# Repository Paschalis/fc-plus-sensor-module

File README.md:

# FC Plus Sensor Module

**FC Plus** is a modular add-on board designed for UAV flight controllers, providing advanced telemetry, GPS, object avoidance (ToF, Sonar, IR), and LED indicators for status feedback. This repository contains the necessary documentation, hardware setup guides, sensor integration instructions, and communication protocols (LoRa/WiFi) to enhance UAV autonomy and safety.

# Board Designs Overview

This repository contains a collection of **FC Plus Sensor Modules Boards** categorized by their transmission modes. More details about the transmission modes can be found in the [Transmission Modes Classification](SensorFCPlus/README.md).

> **Note:** The PCB colors are used to visually distinguish the boards. The **Antenna Diversity** boards feature **yellow** PCBs, while the **True Diversity** boards are **blue**. The **Gemini Mode** boards are marked with **red** PCBs, and the **Gemini Xrossband (GemX)** boards are designed with **purple** PCBs for easy identification.

<p align="center">
    
</p>

## 1. Antenna Diversity Boards (Yellow Boards)

### FC Plus Sensor Modules Boards at 2.4GHz

| Name            | Features                                                        | Preview                                                       |
|-----------------|-----------------------------------------------------------------|---------------------------------------------------------------|
| V1-M10Q-HMC     | GPS: SAM-M10Q, MAG: HMC5883L, ELRS: 2.4GHz RX                   |  <p align="center"> Click on the image to view the files </p>|
| V2-M10Q-QMC     | GPS: SAM-M10Q, MAG: QMC5883L, ELRS: 2.4GHz RX                   |  <p align="center"> Click on the image to view the files </p>|
| V3-M10Q-LSM     | GPS: SAM-M10Q, MAG: LSM303AH, ELRS: 2.4GHz RX                   |  <p align="center"> Click on the image to view the files </p> |

### FC Plus Sensor Modules Boards at 900MHz

<details>
<summary>Click to view Antenna Diversity Boards at 900MHz</summary>

| Name            | Features                                                        | Preview                                                       |
|-----------------|-----------------------------------------------------------------|---------------------------------------------------------------|
| V1-M10Q-HMC     | GPS: SAM-M10Q, MAG: HMC5883L, ELRS: 900MHz RX                   |  |
| V2-M10Q-QMC     | GPS: SAM-M10Q, MAG: QMC5883L, ELRS: 900MHz RX                   |  |
| V3-M10Q-LSM     | GPS: SAM-M10Q, MAG: LSM303AH, ELRS: 900MHz RX                   |  |

</details>

---
> **Note:** In the following boards, the **LSM303AH** magnetometer was selected over other options due to its **better overall performance**, offering improved accuracy and reliability in magnetic field sensing. The **MAX-M10S** GPS module was chosen instead of the SAM-M10Q for its **lower cost** while still providing good performance for navigation, making it a more economical choice for the boards.

## 2. True Diversity Boards (Blue Boards)

### FC Plus Sensor Modules Boards at 2.4GHz
| Name            | Features                                                        | Preview                                                       |
|-----------------|-----------------------------------------------------------------|---------------------------------------------------------------|
| TD-M10S-LSM     | GPS: MAX-M10S, MAG: LSM303AH, ELRS: 2.4GHz RX                   |  <p align="center"> Click on the image to view the files </p>|

### FC Plus Sensor Modules Boards at 900MHz
<details>
<summary>Click to view True Diversity Boards at 900MHz</summary>

| Name            | Features                                                        | Preview                                                       |
|-----------------|-----------------------------------------------------------------|---------------------------------------------------------------|
| TD-M10S-LSM     | GPS: MAX-M10S, MAG: LSM303AH, ELRS: 900MHz RX                   |  |

</details>

## 3. Gemini Mode Boards

> **Note:**  
> - The **Gemini boards** are actually the **True Diversity boards** operating in **Gemini Mode**.  
> - To enable **Gemini Mode**, set the **RX Antenna Mode** to **Gemini** via Lua script.  
> - **Single Antenna RX boards** can also operate in Gemini Mode but must use **Model 5** in **Model Config Matching** via Lua script.  
> - **Gemini-capable receivers** should use **Model 6** in **Model Config Matching**.  
> - Click on [🔗 **Go to True Diversity Full Diversity Boards (Blue Boards)**](#2-true-diversity-boards-blue-boards) to view compatible receivers.  
>  
> 📖 **Reference:** [ExpressLRS Gemini Mode Documentation](https://www.expresslrs.org/software/gemini/#what-is-gemini)  

## 4. Gemini Xrossband (GemX) Boards (Purple Boards)

### FC Plus Sensor Modules Boards
| Name            | Features                                                        | Preview                                                       |
|-----------------|-----------------------------------------------------------------|---------------------------------------------------------------|
| GemX-M10S-LSM     | GPS: MAX-M10S, MAG: LSM303AH, ELRS: 2.4GHz and 900MHz RX      |  |

## Related Projects

### **Autonomous UAVs: MAVLink Communication Between FCs and SBCs**
This repository explores MAVLink communication between flight controllers and SBCs, enabling UAV autonomy with features like peripheral integration and real-time image processing.

<div align="center">

</div>

Explore more about the **MAVLink Communication Between FCs and SBCs** project and its integration into autonomous UAVs by clicking on the badge above to access the full documentation and setup guide.

### **Custom RX/TX Board Designs for GCS Communication**

This repository provides a receiver and transmitter solution for Ground Control Stations (GCS), designed to provide reliable telemetry and control using ELRS, mLRS, and MAVLink protocols. Featuring board designs optimized for long-range communication, minimal latency, and robust performance under varying conditions, these boards cater to diverse operational needs for UAV telemetry systems.

<div align="center">

</div>

Explore the **Custom RX/TX Board Designs for GCS Communication** project and its integration into UAV telemetry systems by clicking on the badge above.

## Contributing

Your contributions and suggestions are crucial for the improvement of this project!  Feel free to submit pull requests or open issues if you encounter any problems.

## License

This project is licensed under the [GPLv3 License](https://opensource.org/licenses/GPL-3.0) - see the [LICENSE](LICENSE) file for details.

---

**Thank you for visiting fc-plus-sensor-module!**

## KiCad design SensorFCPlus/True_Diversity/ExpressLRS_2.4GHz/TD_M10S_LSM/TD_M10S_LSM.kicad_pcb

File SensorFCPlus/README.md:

# Transmission Modes Classification

This document describes various transmission modes used in long-range LoRa (Long Range) wireless communication for drones. These modes leverage LoRa's unique capabilities to improve Signal Quality (LQ), mitigate interference, and enhance reliability over extended distances, making them ideal for drone applications in diverse environments.
## Transmission Modes

### 1. Single Antenna
- **Description**:  
  Uses one antenna on both the transmitter and receiver, operating over a single frequency channel.
- **Advantages**:  
  - Simplicity  
  - Low cost  
- **Limitations**:  
  - Highly susceptible to interference and signal loss.  

### 2. Antenna Diversity

- **Description**:  
  The receiver employs two antennas to select the best signal, while the transmitter uses a single antenna. Communication occurs over a single frequency channel.  
- **Advantages**:  
  - Improved signal quality due to antenna selection.  
- **Limitations**:  
  - Only one frequency channel is used.  
  - Transmission lacks diversity.  

### 3. True Diversity or Full Diversity
- **Description**:  
  Both the transmitter and receiver utilize two independent Semtech LoRa chips, each connected to its own antenna, operating on the same frequency. This setup provides full diversity for both transmitting and receiving.  
- **Advantages**:  
  - Enhanced signal quality through full transmitter and receiver diversity.  
  - Redundancy in signal transmission and reception.  
- **Limitations**:  
  - Increased complexity and cost.  

### 4. Gemini Mode (Single Band)
- **Description**:  
  The transmitter sends packets on two frequencies within the same band (e.g., 2.4 GHz or 900 MHz), spaced approximately 40 MHz apart for 2.4 GHz and 10 MHz apart for 900 MHz. A true diversity receiver with two antennas and LoRa chips receives both signals simultaneously.  
- **Advantages**:  
  - Superior interference mitigation by utilizing two frequencies within the same band.  
  - Improved stability and reliability of signal quality.  
- **Limitations**:  
  - Limited to a single frequency band.  

### 5. Gemini Xrossband GemX (Dual Band)
- **Description**:  
  The transmitter operates simultaneously on two different frequency bands (e.g., 2.4 GHz and 900 MHz), each managed by independent LoRa chips. The receiver employs true diversity hardware with two antennas and LoRa chips operating on distinct bands.  
- **Advantages**:  
  - Enhanced interference avoidance by operating across separate bands.  
  - Increased performance and redundancy for long-range communication.  
- **Limitations**:  
  - More complex and expensive hardware due to dual-band operation.  

---

## Transmission Mode Classification Chart

| Mode                        | Frequency Channels      | Antennas (TX) | Antennas (RX)| Interference Mitigation | Signal Quality  | Receiver Type        |
|-----------------------------|-------------------------|---------------|---------------|-------------------------|-----------------|----------------------|
| **Single Antenna**          | 1                      | 1             | 1             | Low                     | Low             | Simple Receiver      |
| **Antenna Diversity**       | 1                      | 1             | 2             | Moderate                | Moderate        | Diversity Receiver   |
| **True Diversity or Full Diversity**  | 1                      | 1             | 2             | High                    | High            | Diversity Receiver   |
| **Gemini Mode (Single Band)**| 2 (within 1 band)     | 2        | 2             | Very High               | Very High       | Diversity Receiver   |
| **Gemini Xrossband GemX (Dual Band)** | 2 (across 2 bands)     | 2             | 2                | Excellent               | Excellent       | Dual-band Receiver   |

---

## Summary

This classification illustrates the progression from basic single antenna setups to advanced true diversity and dual-band configurations:

- **Single Antenna** and **Antenna Diversity** provide fundamental solutions suitable for simple environments.  
- **True Diversity** or **Full Diversity** and **Gemini Mode (Single Band)** offer significant enhancements in reliability and interference mitigation within the same band.  
- **Gemini Xrossband GemX (Dual Band)** delivers optimal performance by leveraging dual-band communication, ideal for complex and interference-prone environments.  

Understanding these modes enables the selection of appropriate communication systems tailored to specific drone operation requirements, ensuring robust and efficient wireless links.

---

## References

- [mLRS GitHub Repository](https://github.com/olliw42/mLRS)  
- [mLRS Documentation](https://github.com/olliw42/mLRS-docu)  
- [mLRS Hardware Repository](https://github.com/olliw42/mLRS-hardware/tree/master)  
- [ArduPilot: mLRS RC Overview](https://ardupilot.org/copter/docs/common-mlrs-rc.html)  
- [ExpressLRS: Gemini Overview](https://www.expresslrs.org/software/gemini/)  
- [ExpressLRS Documentation](https://www.expresslrs.org/)  

[⬅️ Go Back to Main README](../README.md)

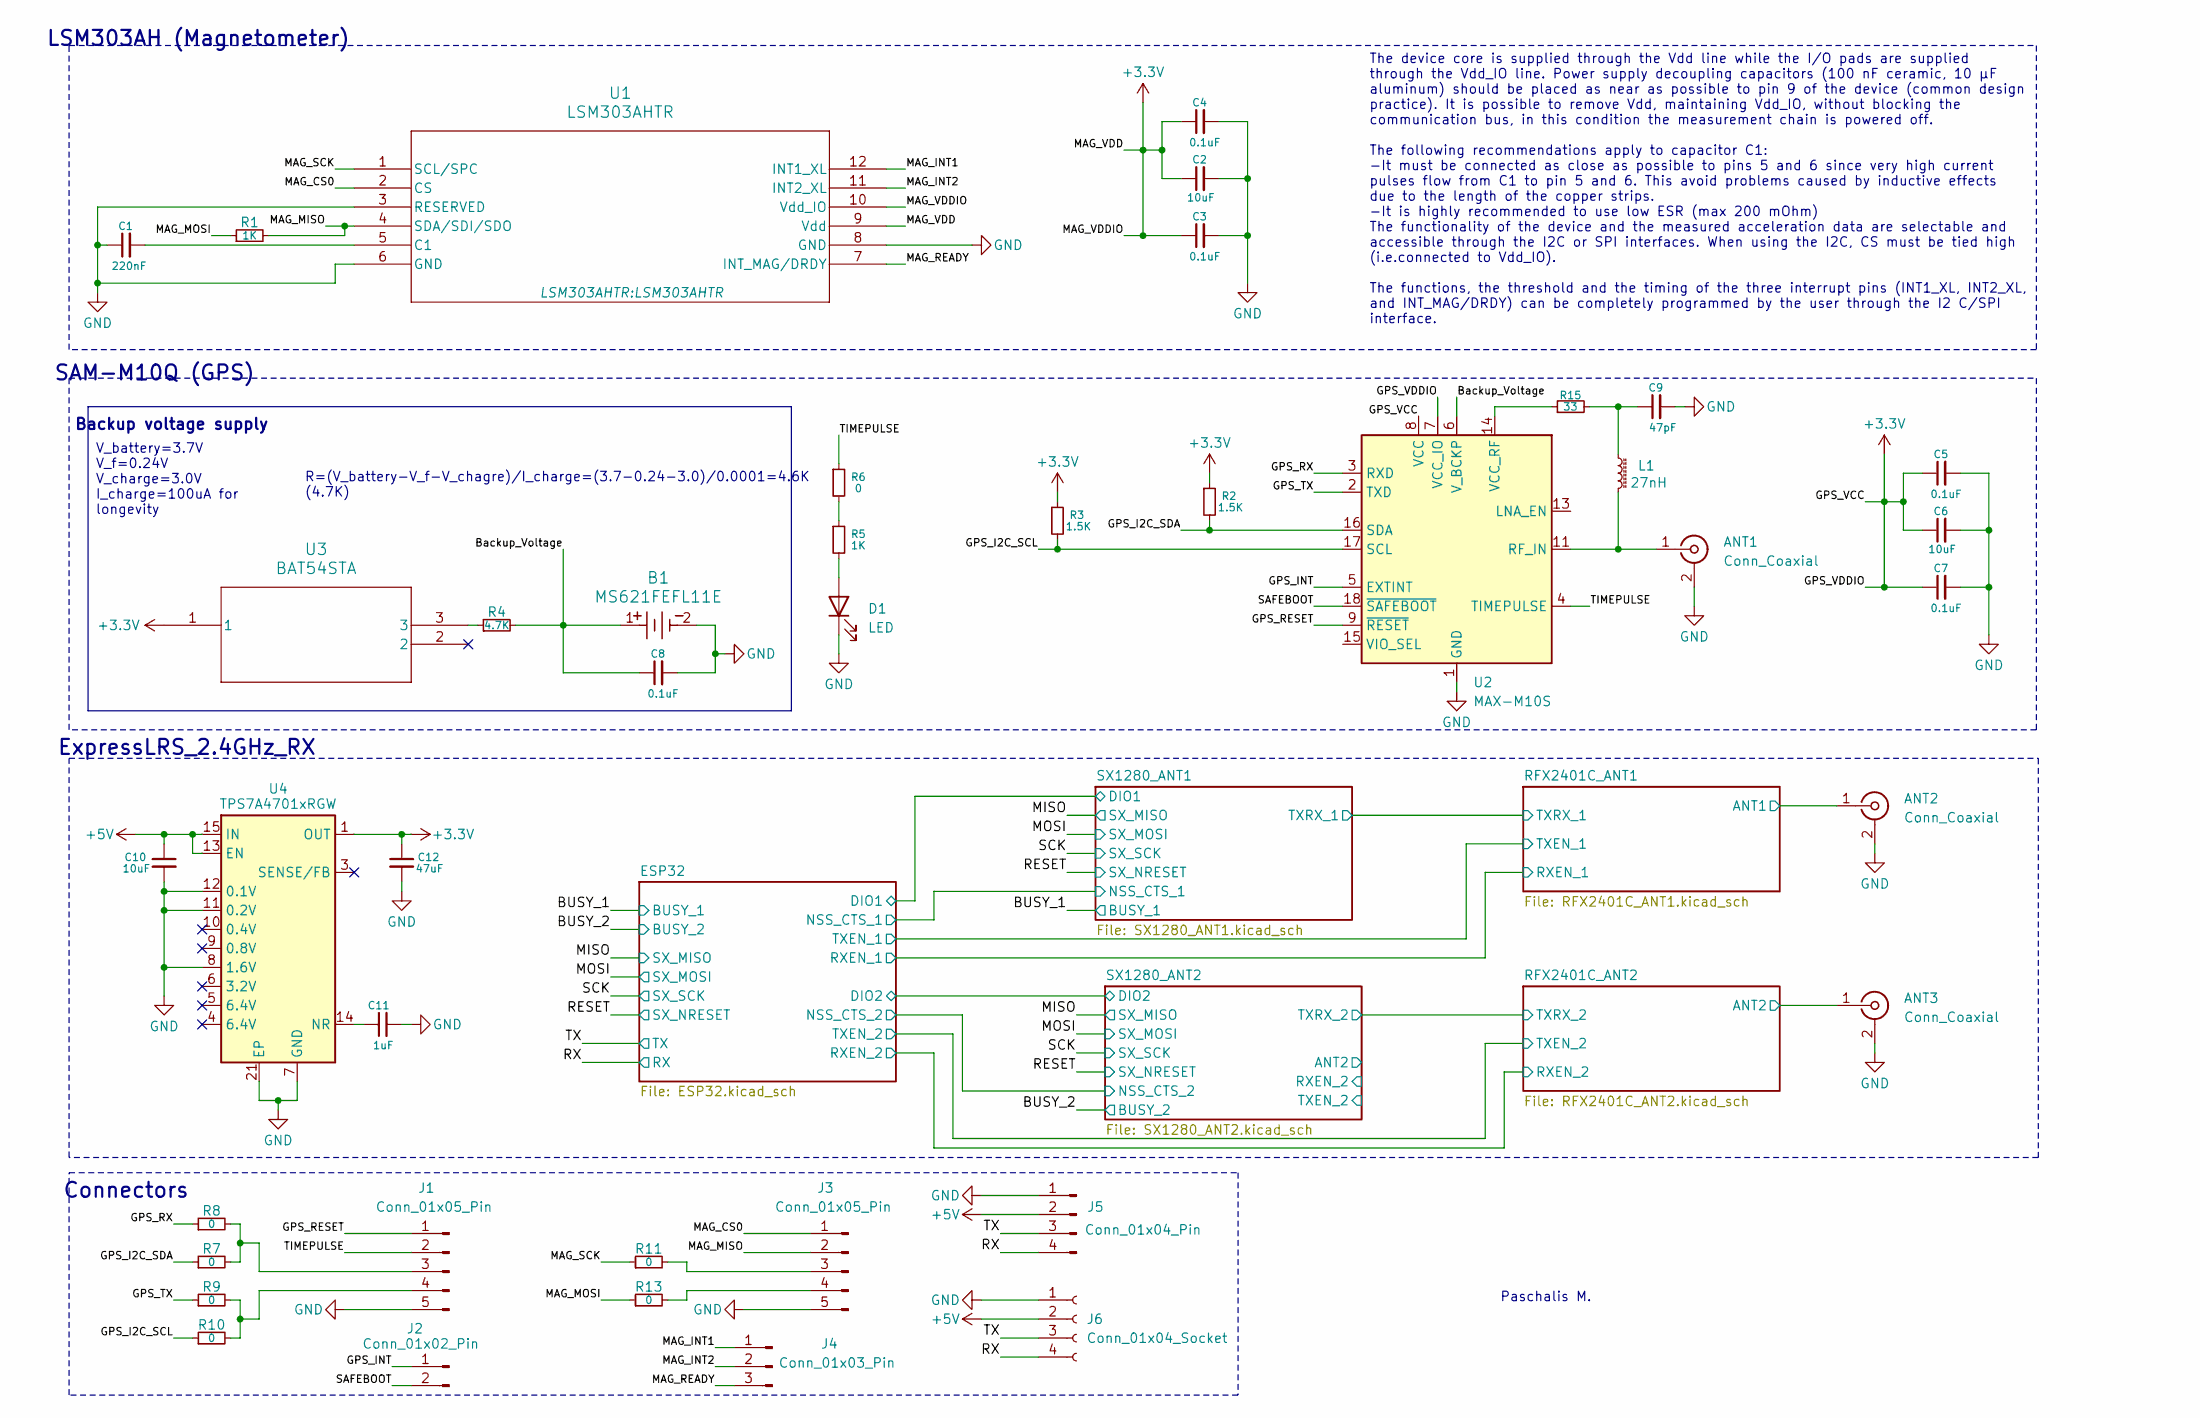
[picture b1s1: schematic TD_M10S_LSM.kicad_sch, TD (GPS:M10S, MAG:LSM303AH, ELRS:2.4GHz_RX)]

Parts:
ANT1, ANT2, ANT3: Conn_Coaxial; U.FL_Hirose_U.FL-R-SMT-1_Vertical
B1: MS621FEFL11E; MS621FE-FL11E
C1: 220nF; C_0603_1608Metric_Pad1.08x0.95mm_HandSolder
C2, C6: 10uF; ECASD40J106M055K00
C3, C4, C5, C7, C8: 0.1uF; C_0603_1608Metric_Pad1.08x0.95mm_HandSolder
C9: 47pF; C_0603_1608Metric_Pad1.08x0.95mm_HandSolder
C10: 10uF; C_0603_1608Metric_Pad1.08x0.95mm_HandSolder
C11: 1uF; C_0603_1608Metric_Pad1.08x0.95mm_HandSolder
C12: 47uF; C_0603_1608Metric_Pad1.08x0.95mm_HandSolder
D1: LED; LED_0805_2012Metric_Pad1.15x1.40mm_HandSolder
J1, J3: Conn_01x05_Pin; PinHeader_1x05_P2.00mm_Vertical
J2: Conn_01x02_Pin; PinHeader_1x02_P2.00mm_Vertical
J4: Conn_01x03_Pin; PinHeader_1x03_P2.00mm_Vertical
J5: Conn_01x04_Pin; JST_GH_SM04B-GHS-TB_1x04-1MP_P1.25mm_Horizontal
J6: Conn_01x04_Socket; Harwin_M20-89004xx_1x04_P2.54mm_Horizontal
L1: 27nH; L_6.3x6.3_H3
R1, R5: 1K; R_0603_1608Metric_Pad0.98x0.95mm_HandSolder
R2, R3: 1.5K; R_0603_1608Metric_Pad0.98x0.95mm_HandSolder
R4: 4.7K; R_0603_1608Metric_Pad0.98x0.95mm_HandSolder
R6, R7, R8, R9, R10, R11, R13: 0; R_0603_1608Metric_Pad0.98x0.95mm_HandSolder
R15: 33; R_0603_1608Metric_Pad0.98x0.95mm_HandSolder
U1: LSM303AHTR
U2: MAX-M10S; ublox_MAX
U3: BAT54STA
U4: TPS7A4701xRGW; Texas_RGW0020A_VQFN-20-1EP_5x5mm_P0.65mm_EP3.15x3.15mm_Ther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

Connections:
+3.3V: C2.1, C3.1, C4.1, C5.1, C6.1, C7.1, C12.1, R2.1, R3.1, U1.9 (Vdd), U1.10 (Vdd_IO), U2.7 (VCC_IO), U2.8 (VCC), U3.1, U4.1 (OUT), U4.20 (OUT); also elsewhere on the board
+5V: C10.1, J5.2, J6.2, U4.13 (EN), U4.15 (IN), U4.16 (IN); also elsewhere on the board
/Backup_Voltage: B1.1, C8.1, R4.2, U2.6 (V_BCKP)
/GPS_I2C_SCL: R3.2, R10.1, U2.17 (SCL)
/GPS_I2C_SDA: R2.2, R7.1, U2.16 (SDA)
/GPS_INT: J2.1, U2.5 (EXTINT)
/GPS_RESET: J1.1, U2.9 (~RESET)
/GPS_RX: R8.1, U2.3 (RXD)
/GPS_TX: R9.1, U2.2 (TXD)
/MAG_CS0: J3.1, U1.2 (CS)
/MAG_INT1: J4.1, U1.12 (INT1_XL)
/MAG_INT2: J4.2, U1.11 (INT2_XL)
/MAG_MISO: J3.2, R1.2, U1.4 (SDA/SDI/SDO)
/MAG_MOSI: R1.1, R13.1
/MAG_READY: J4.3, U1.7 (INT_MAG/DRDY)
/MAG_SCK: R11.1, U1.1 (SCL/SPC)
/RFX2401C_ANT1/ANT1: ANT2.1 (In); also elsewhere on the board
/RFX2401C_ANT2/ANT2: ANT3.1 (In); also elsewhere on the board
/RX: J5.4, J6.4; also elsewhere on the board
/SAFEBOOT: J2.2, U2.18 (~SAFEBOOT)
/TIMEPULSE: J1.2, R6.1, U2.4 (TIMEPULSE)
/TX: J5.3, J6.3; also elsewhere on the board
GND: ANT1.2 (Ext), ANT2.2 (Ext), ANT3.2 (Ext), B1.2, C1.1, C2.2, C3.2, C4.2, C5.2, C6.2, C7.2, C8.2, C9.2, C10.2, C11.2, C12.2, D1.1 (K), J1.5, J3.5, J5.1, J6.1, U1.3 (RESERVED), U1.6 (GND), U1.8 (GND), U2.1 (GND), U2.10 (GND), U2.12 (GND), U4.7 (GND), U4.8 (1.6V), U4.11 (0.2V), U4.12 (0.1V), U4.21 (EP); also elsewhere on the board
unnamed: ANT1.1 (In), L1.2, U2.11 (RF_IN)
unnamed: C9.1, L1.1, R15.2
unnamed: D1.2 (A), R5.2
unnamed: J1.3, R7.2, R8.2
unnamed: J1.4, R9.2, R10.2
unnamed: J3.3, R11.2
unnamed: J3.4, R13.2
unnamed: R4.1, U3.3
unnamed: R5.1, R6.2
unnamed: C1.2, U1.5 (C1)
unnamed: R15.1, U2.14 (VCC_RF)
unnamed: C11.1, U4.14 (NR)

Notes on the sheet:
Backup voltage supply
Paschalis M.
Connectors
SAM-M10Q (GPS)
LSM303AH (Magnetometer)
ExpressLRS_2.4GHz_RX
The device core is supplied through the Vdd line while the I/O pads are supplied through the Vdd_IO line. Power supply decoupling capacitors (100 nF ceramic, 10 μF aluminum) should be placed as near as possible to pin 9 of the device (common design practice). It is possible to remove Vdd, maintaini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
V_battery=3.7V V_f=0.24V V_charge=3.0V I_charge=100uA for longevity
R=(V_battery-V_f-V_chagre)/I_charge=(3.7-0.24-3.0)/0.0001=4.6K (4.7K)

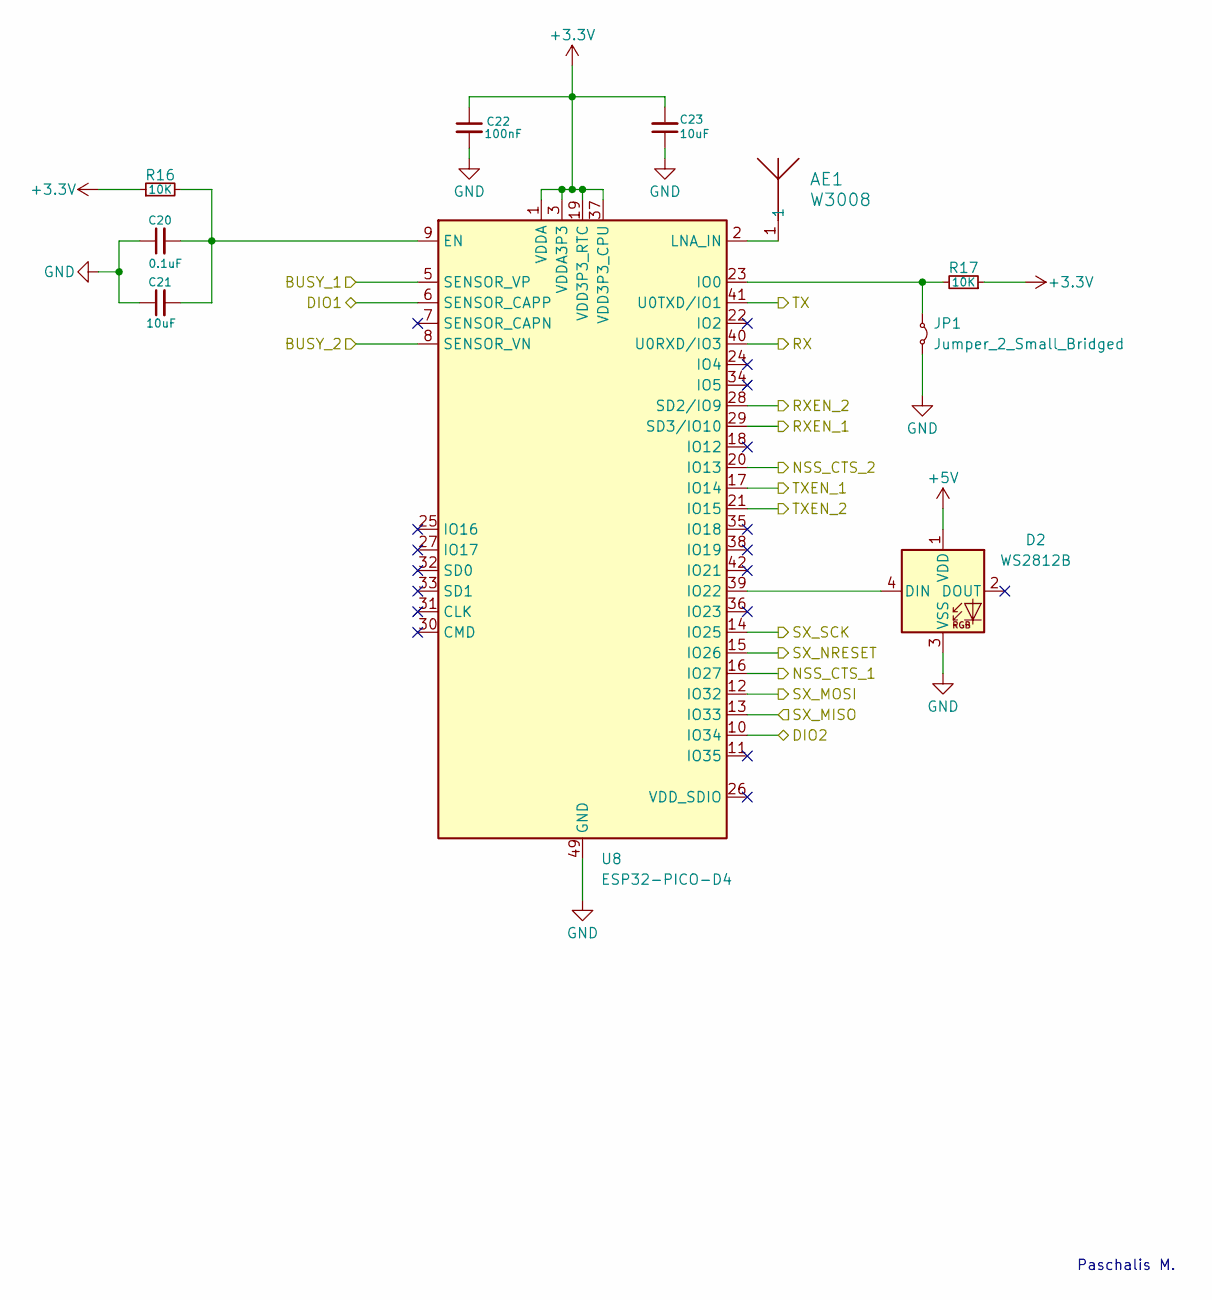
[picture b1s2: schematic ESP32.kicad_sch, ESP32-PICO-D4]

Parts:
AE1: W3008; ANT_W3008_PUL
C20: 0.1uF; C_0603_1608Metric_Pad1.08x0.95mm_HandSolder
C21, C23: 10uF; ECASD40J106M055K00
C22: 100nF; C_0603_1608Metric_Pad1.08x0.95mm_HandSolder
D2: WS2812B; LED_WS2812B_PLCC4_5.0x5.0mm_P3.2mm
JP1: Jumper_2_Small_Bridged; TestPoint_2Pads_Pitch2.54mm_Drill0.8mm
R16, R17: 10K; R_0603_1608Metric_Pad0.98x0.95mm_HandSolder
U8: ESP32-PICO-D4; QFN-48-1EP_7x7mm_P0.5mm_EP5.1x5.1mm_ThermalVias

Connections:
+3.3V: C22.1, C23.2, R16.1, R17.1, U8.1 (VDDA), U8.3 (VDDA3P3), U8.4 (VDDA3P3), U8.19 (VDD3P3_RTC), U8.37 (VDD3P3_CPU), U8.43 (VDDA), U8.46 (VDDA); also elsewhere on the board
+5V: D2.1 (VDD); also elsewhere on the board
/BUSY_1: U8.5 (SENSOR_VP); also elsewhere on the board
/BUSY_2: U8.8 (SENSOR_VN); also elsewhere on the board
/ESP32/DIO1: U8.6 (SENSOR_CAPP); also elsewhere on the board
/ESP32/DIO2: U8.10 (IO34); also elsewhere on the board
/ESP32/NSS_CTS_1: U8.16 (IO27); also elsewhere on the board
/ESP32/NSS_CTS_2: U8.20 (IO13); also elsewhere on the board
/ESP32/RXEN_1: U8.29 (SD3/IO10); also elsewhere on the board
/ESP32/RXEN_2: U8.28 (SD2/IO9); also elsewhere on the board
/ESP32/TXEN_1: U8.17 (IO14); also elsewhere on the board
/ESP32/TXEN_2: U8.21 (IO15); also elsewhere on the board
/MISO: U8.13 (IO33); also elsewhere on the board
/MOSI: U8.12 (IO32); also elsewhere on the board
/RESET: U8.15 (IO26); also elsewhere on the board
/RX: U8.40 (U0RXD/IO3); also elsewhere on the board
/SCK: U8.14 (IO25); also elsewhere on the board
/TX: U8.41 (U0TXD/IO1); also elsewhere on the board
GND: C20.1, C21.1, C22.2, C23.1, D2.3 (VSS), JP1.2 (B), U8.49 (GND); also elsewhere on the board
unnamed: D2.4 (DIN), U8.39 (IO22)
unnamed: JP1.1 (A), R17.2, U8.23 (IO0)
unnamed: C20.2, C21.2, R16.2, U8.9 (EN)
unnamed: AE1.1, U8.2 (LNA_IN)

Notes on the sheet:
Paschalis M.

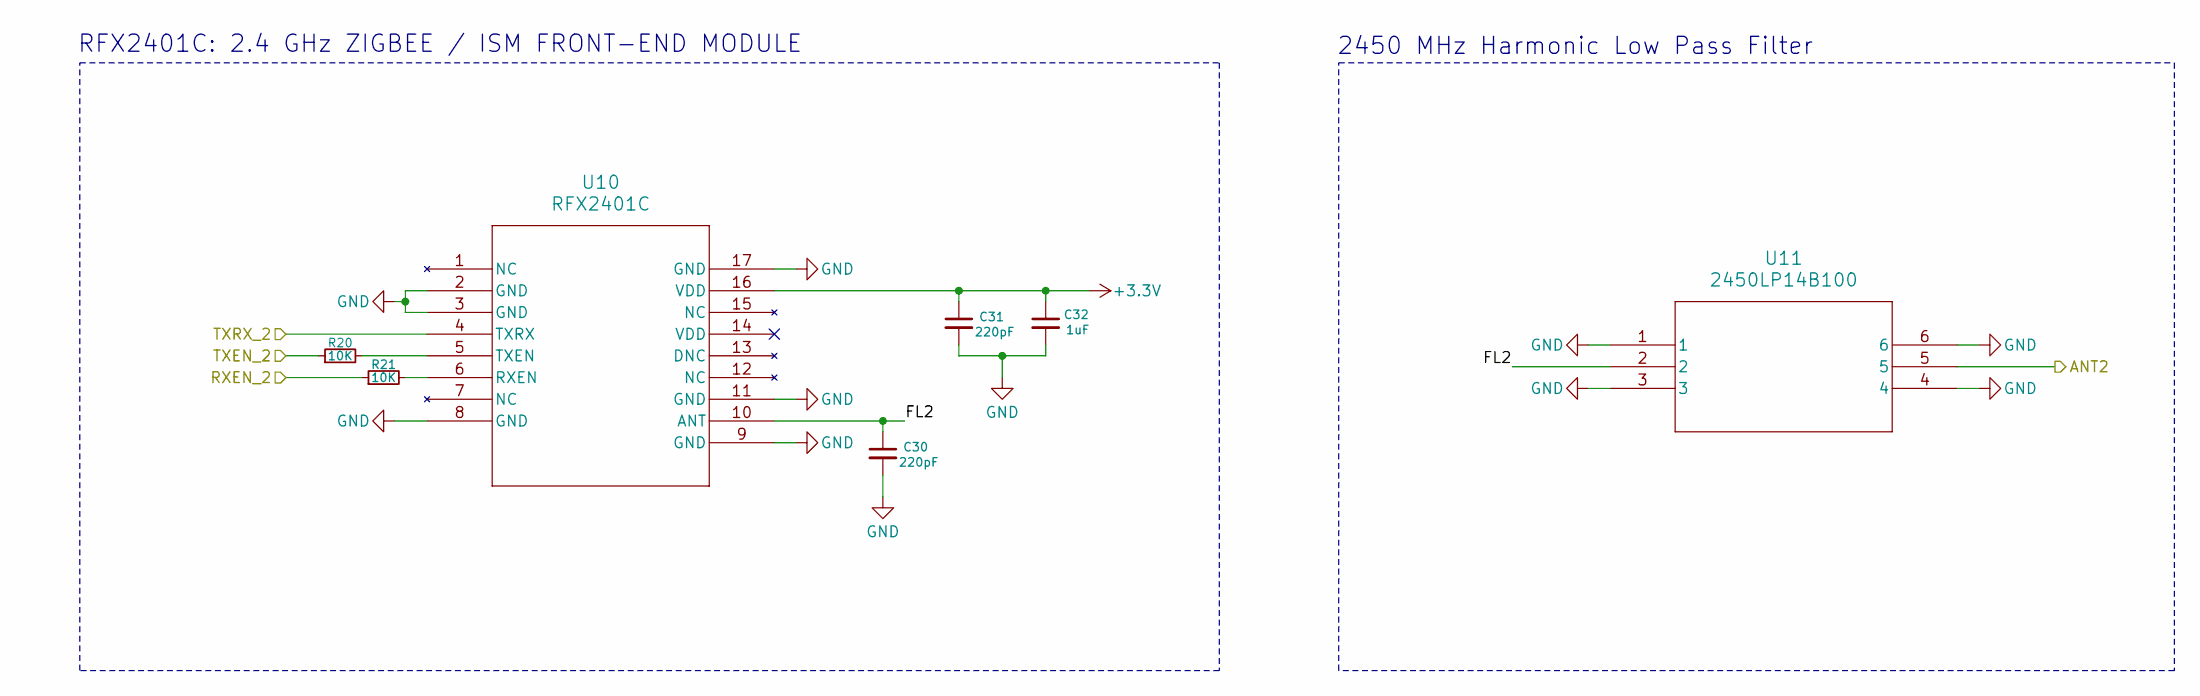
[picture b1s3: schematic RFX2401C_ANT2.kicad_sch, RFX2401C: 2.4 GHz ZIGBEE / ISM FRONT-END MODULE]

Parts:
C30, C31: 220pF; C_0603_1608Metric_Pad1.08x0.95mm_HandSolder
C32: 1uF; C_0603_1608Metric_Pad1.08x0.95mm_HandSolder
R20, R21: 10K; R_0603_1608Metric_Pad0.98x0.95mm_HandSolder
U10: RFX2401C; RFX2401C_SKY
U11: 2450LP14B100; CHIP_SMD_1P6XP8_JOD

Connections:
+3.3V: C31.1, C32.1, U10.16 (VDD); also elsewhere on the board
/ESP32/RXEN_2: R21.1; also elsewhere on the board
/ESP32/TXEN_2: R20.1; also elsewhere on the board
/RFX2401C_ANT2/ANT2: U11.5; also elsewhere on the board
/RFX2401C_ANT2/FL2: C30.1, U10.10 (ANT), U11.2
/RFX2401C_ANT2/TXRX_2: U10.4 (TXRX); also elsewhere on the board
GND: C30.2, C31.2, C32.2, U10.2 (GND), U10.3 (GND), U10.8 (GND), U10.9 (GND), U10.11 (GND), U10.17 (GND), U11.1, U11.3, U11.4, U11.6; also elsewhere on the board
unnamed: R21.2, U10.6 (RXEN)
unnamed: R20.2, U10.5 (TXEN)

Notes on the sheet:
RFX2401C: 2.4 GHz ZIGBEE / ISM FRONT-END MODULE
2450 MHz Harmonic Low Pass Filter

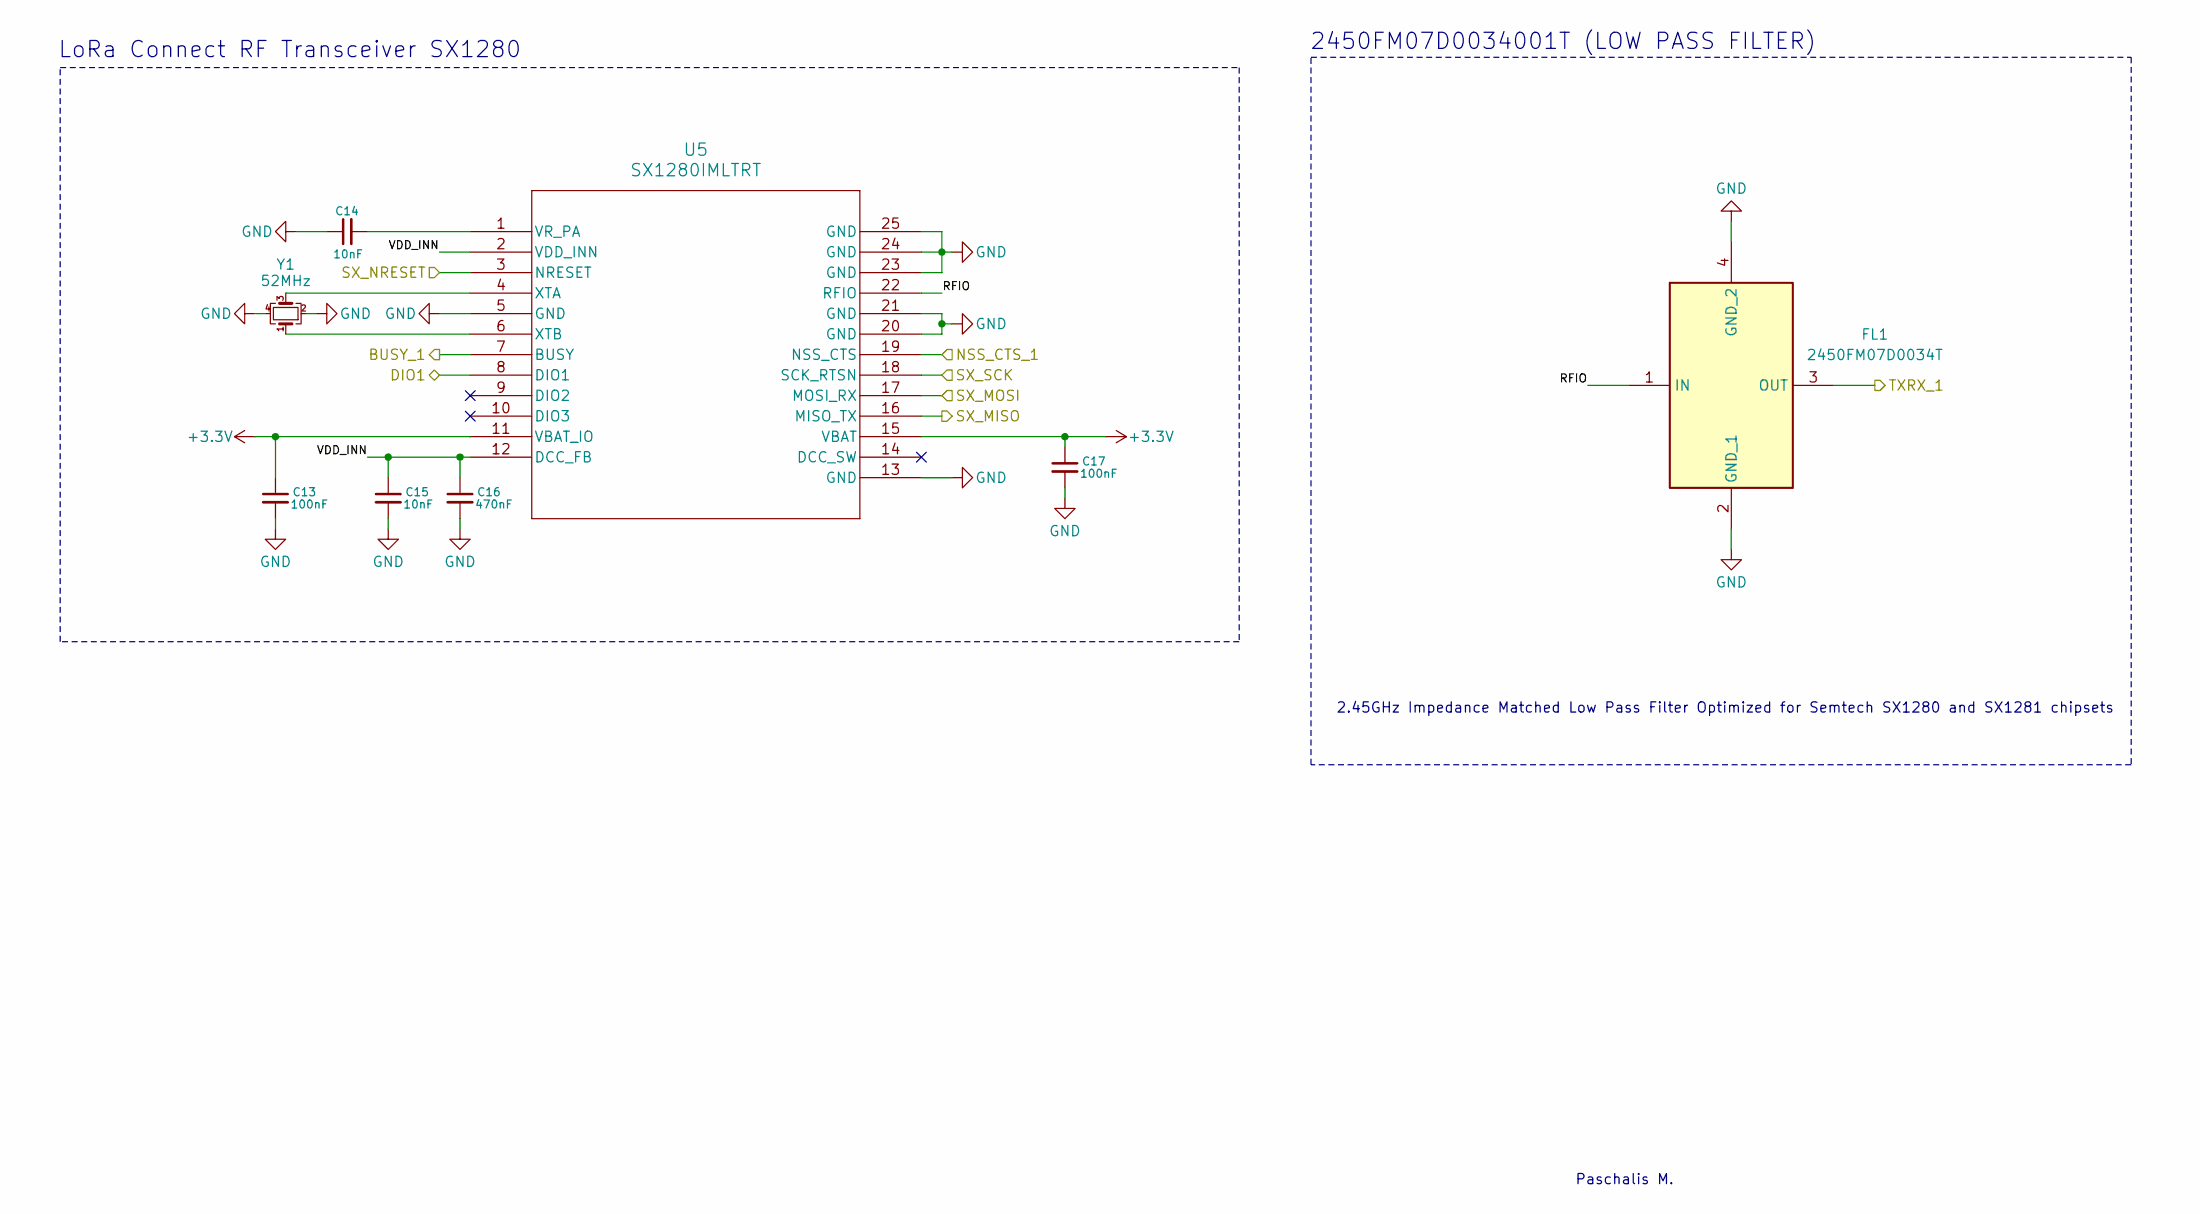
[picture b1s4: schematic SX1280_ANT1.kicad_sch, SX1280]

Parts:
C13, C17: 100nF; C_0603_1608Metric_Pad1.08x0.95mm_HandSolder
C14, C15: 10nF; C_0603_1608Metric_Pad1.08x0.95mm_HandSolder
C16: 470nF; C_0603_1608Metric_Pad1.08x0.95mm_HandSolder
FL1: 2450FM07D0034T; Mouser Part Number 609-2450FM07D0034T
U5: SX1280IMLTRT; QFN24_4X4_SEM
Y1: 52MHz; Crystal_SMD_2016-4Pin_2.0x1.6mm

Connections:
+3.3V: C13.1, C17.1, U5.11 (VBAT_IO), U5.15 (VBAT); also elsewhere on the board
/BUSY_1: U5.7 (BUSY); also elsewhere on the board
/ESP32/DIO1: U5.8 (DIO1); also elsewhere on the board
/ESP32/NSS_CTS_1: U5.19 (NSS_CTS); also elsewhere on the board
/MISO: U5.16 (MISO_TX); also elsewhere on the board
/MOSI: U5.17 (MOSI_RX); also elsewhere on the board
/RESET: U5.3 (NRESET); also elsewhere on the board
/RFX2401C_ANT1/TXRX_1: FL1.3 (OUT); also elsewhere on the board
/SCK: U5.18 (SCK_RTSN); also elsewhere on the board
/SX1280_ANT1/RFIO: FL1.1 (IN), U5.22 (RFIO)
/SX1280_ANT1/VDD_INN: C15.1, C16.1, U5.2 (VDD_INN), U5.12 (DCC_FB)
GND: C13.2, C14.1, C15.2, C16.2, C17.2, FL1.2 (GND_1), FL1.4 (GND_2), U5.5 (GND), U5.13 (GND), U5.20 (GND), U5.21 (GND), U5.23 (GND), U5.24 (GND), U5.25 (GND), Y1.2, Y1.4; also elsewhere on the board
unnamed: C14.2, U5.1 (VR_PA)
unnamed: U5.4 (XTA), Y1.3
unnamed: U5.6 (XTB), Y1.1

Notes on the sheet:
2450FM07D0034001T (LOW PASS FILTER)
2.45GHz Impedance Matched Low Pass Filter Optimized for Semtech SX1280 and SX1281 chipsets
LoRa Connect RF Transceiver SX1280
Paschalis M.

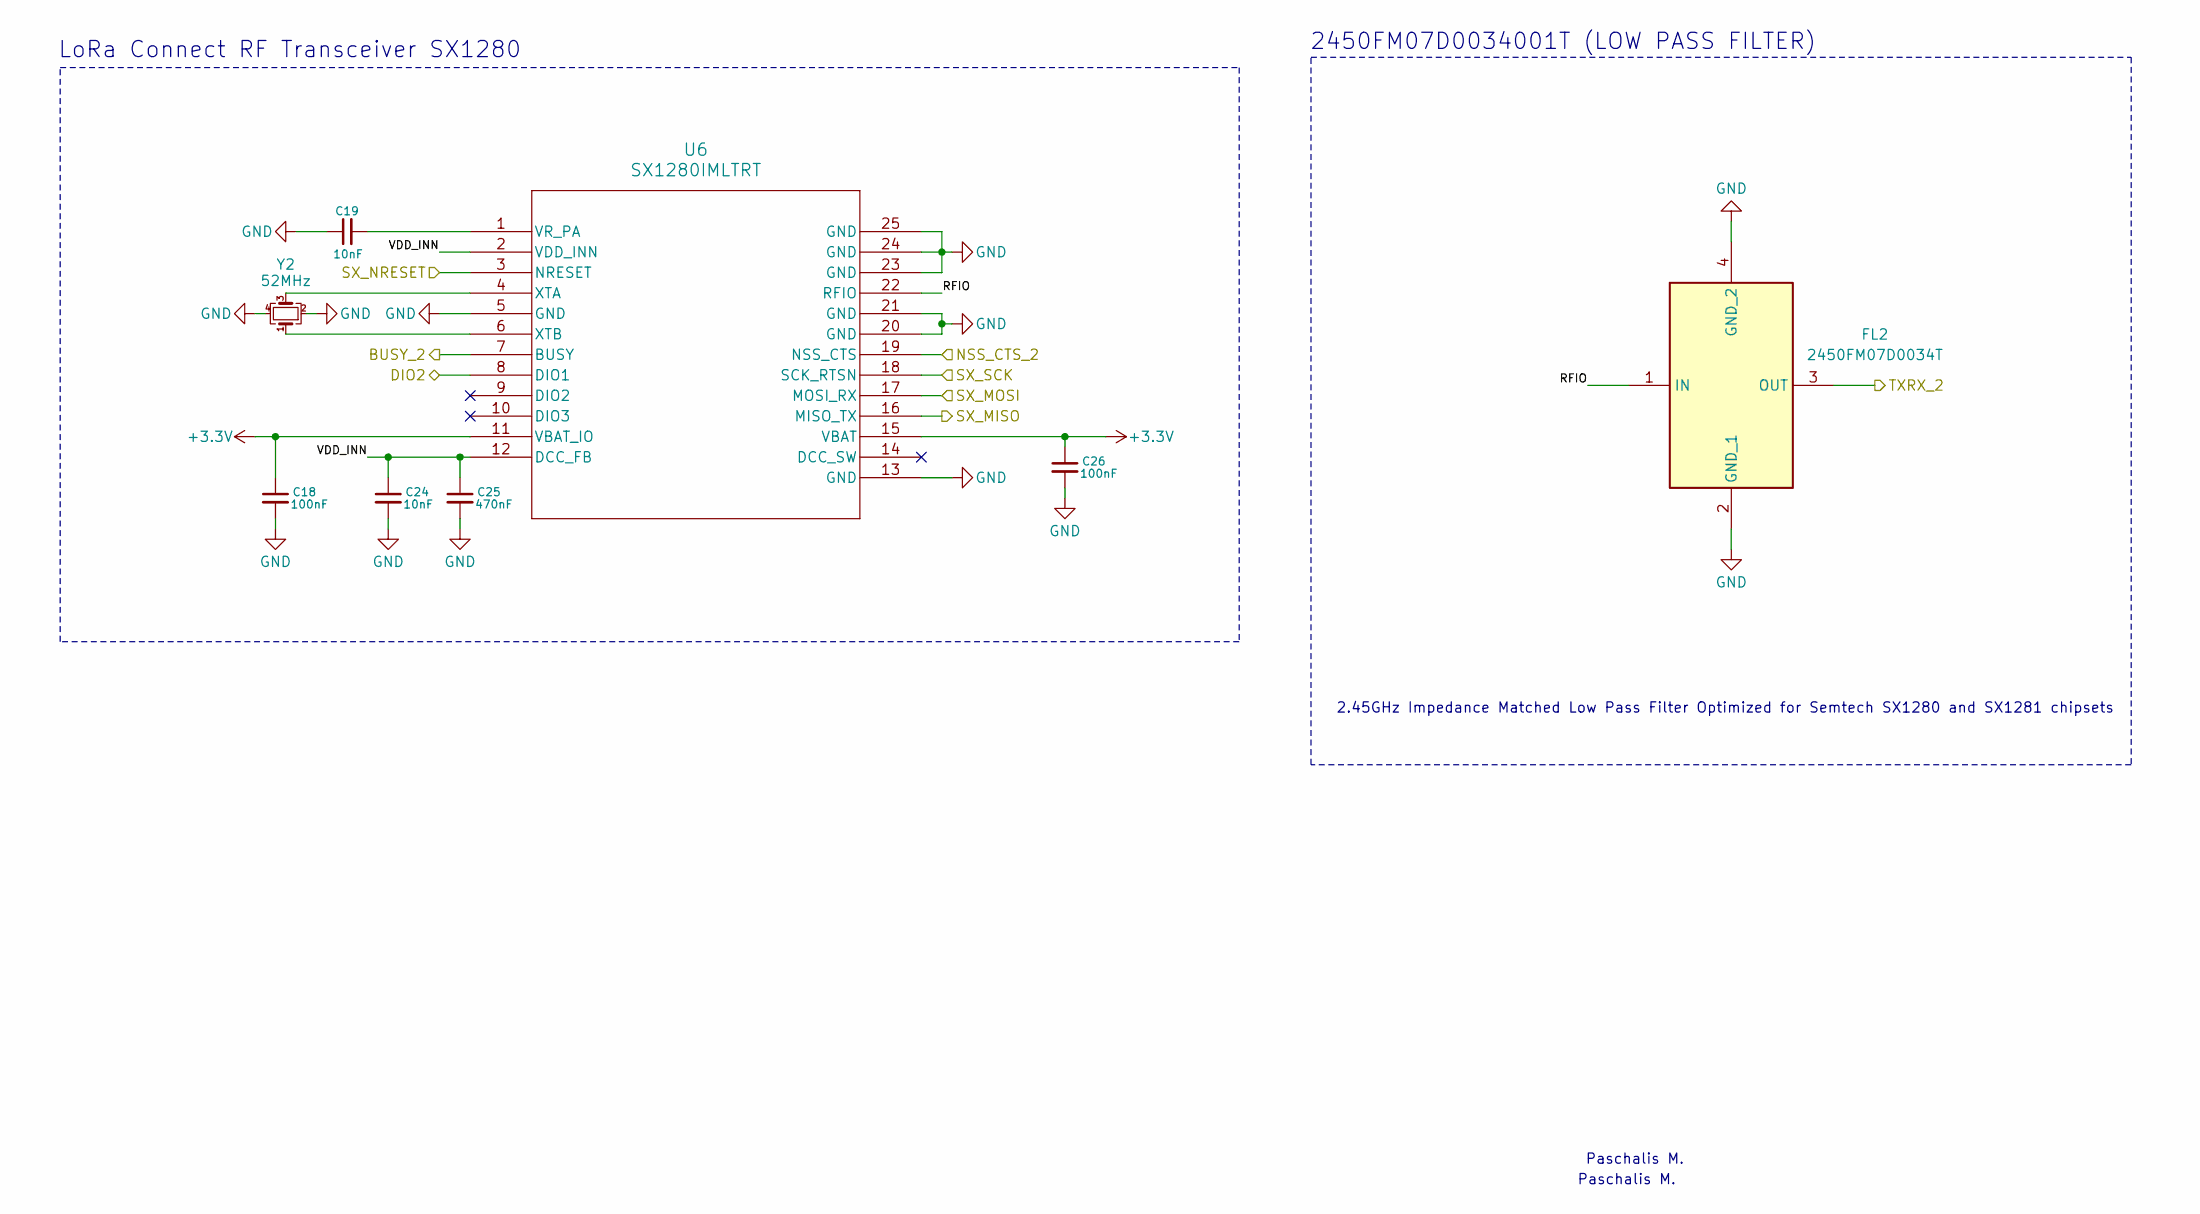
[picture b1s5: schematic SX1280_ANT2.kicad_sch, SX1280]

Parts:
C18, C26: 100nF; C_0603_1608Metric_Pad1.08x0.95mm_HandSolder
C19, C24: 10nF; C_0603_1608Metric_Pad1.08x0.95mm_HandSolder
C25: 470nF; C_0603_1608Metric_Pad1.08x0.95mm_HandSolder
FL2: 2450FM07D0034T; Mouser Part Number 609-2450FM07D0034T
U6: SX1280IMLTRT; QFN24_4X4_SEM
Y2: 52MHz; Crystal_SMD_2016-4Pin_2.0x1.6mm

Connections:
+3.3V: C18.1, C26.1, U6.11 (VBAT_IO), U6.15 (VBAT); also elsewhere on the board
/BUSY_2: U6.7 (BUSY); also elsewhere on the board
/ESP32/DIO2: U6.8 (DIO1); also elsewhere on the board
/ESP32/NSS_CTS_2: U6.19 (NSS_CTS); also elsewhere on the board
/MISO: U6.16 (MISO_TX); also elsewhere on the board
/MOSI: U6.17 (MOSI_RX); also elsewhere on the board
/RESET: U6.3 (NRESET); also elsewhere on the board
/RFX2401C_ANT2/TXRX_2: FL2.3 (OUT); also elsewhere on the board
/SCK: U6.18 (SCK_RTSN); also elsewhere on the board
/SX1280_ANT2/RFIO: FL2.1 (IN), U6.22 (RFIO)
/SX1280_ANT2/VDD_INN: C24.1, C25.1, U6.2 (VDD_INN), U6.12 (DCC_FB)
GND: C18.2, C19.1, C24.2, C25.2, C26.2, FL2.2 (GND_1), FL2.4 (GND_2), U6.5 (GND), U6.13 (GND), U6.20 (GND), U6.21 (GND), U6.23 (GND), U6.24 (GND), U6.25 (GND), Y2.2, Y2.4; also elsewhere on the board
unnamed: C19.2, U6.1 (VR_PA)
unnamed: U6.4 (XTA), Y2.3
unnamed: U6.6 (XTB), Y2.1

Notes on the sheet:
Paschalis M.
LoRa Connect RF Transceiver SX1280
2450FM07D0034001T (LOW PASS FILTER)
2.45GHz Impedance Matched Low Pass Filter Optimized for Semtech SX1280 and SX1281 chipsets
